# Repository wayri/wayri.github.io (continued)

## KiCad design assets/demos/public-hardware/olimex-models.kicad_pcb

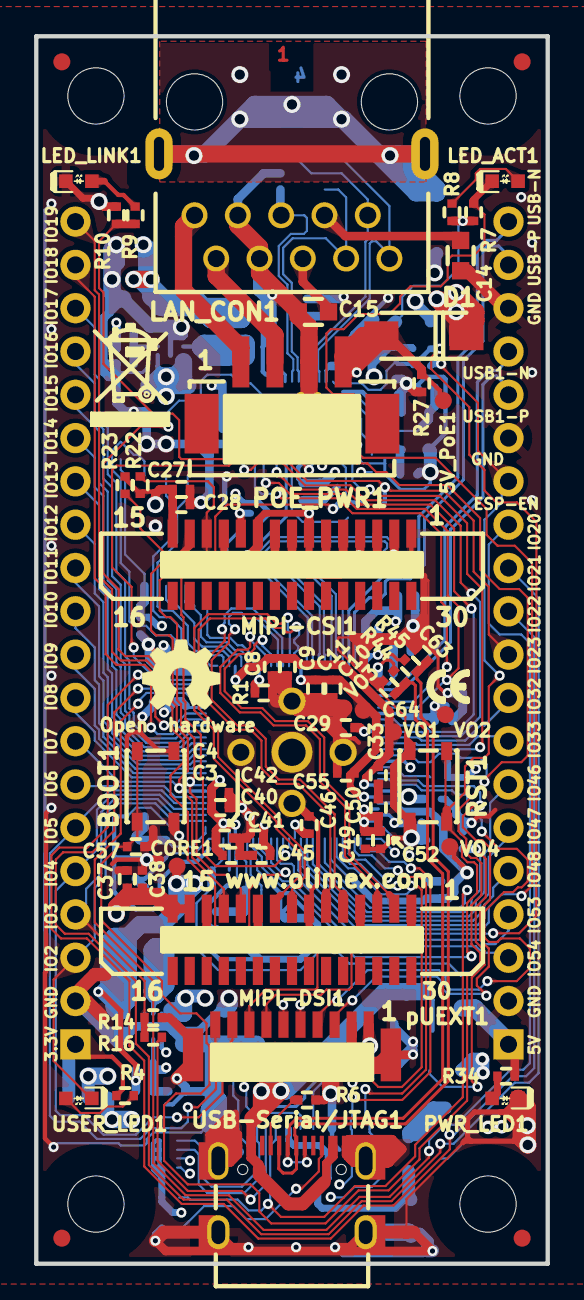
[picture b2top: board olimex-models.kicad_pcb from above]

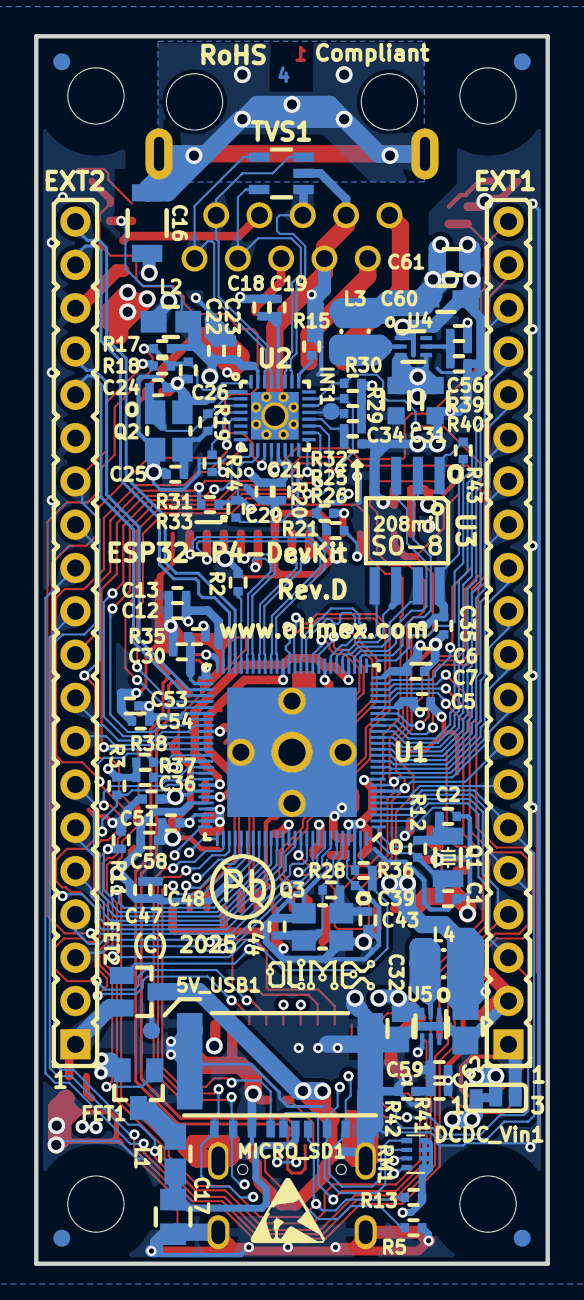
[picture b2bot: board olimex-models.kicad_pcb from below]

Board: 4 copper layers, 30.0 x 72.0 mm, 168 parts (97 on the bottom side), 130 nets.

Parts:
5V_PoE1, 5V_USB1: TESTPAD; TESTPAD_40-ROUND
BOOT1: YTS-A016-X
C1, C2, C43, C44: 22pF/50V/5%/C0G/C0402; C_0402_5MIL_DWS
C3, C6, C18, C20, C22, C27, C37, C40, C49: 10uF/6.3V/20%/X5R/C0402; C_0402_5MIL_DWS
C4, C5, C7, C9, C11, C12, C19, C21, C23, C28, C29, C35, C38, C39, C41, C42, C45, C46, C48, C50, C51, C52, C53: 100nF/10V/20%/X5R/C0402; C_0402_5MIL_DWS
C8, C10, C33, C36, C47, C54, C55, C58: 1uF/6.3V/10%/X5R/C0402; C_0402_5MIL_DWS
C13: 4.7uF/X5R/20%/10V/C0402; C_0402_5MIL_DWS
C14, C15: 100nF/50V/20%/Y5V/C0603; C_0603_5MIL_DWS
C16: 1nF/2000V/10%/X7R/C1206; C_1206_5MIL_DWS_ISO
C17, C62: 47uF/6.3V/20%/X5R/C0805; C_0805_5MIL_DWS
C24, C25: 27pF/50V/5%/C0G/C0402; C_0402_5MIL_DWS
C26: NA(10uF/6.3V/20%/X5R/C0402); C_0402_5MIL_DWS
C30, C57: NA(100nF/10V/20%/X5R/C0402); C_0402_5MIL_DWS
C31, C61: NA(22uF/6.3V/20%/X5R/C0603); C_0603_5MIL_DWS
C32, C34, C60: 22uF/6.3V/20%/X5R/C0603; C_0603_5MIL_DWS
C56, C59: NA(120pF/50V/5%/C0G/C0402); C_0402_5MIL_DWS
C63, C64: NA(150pF/50V/2%/NP0/C0402); C_0402_5MIL_DWS
CORE1: TESTPAD; TESTPAD_40-ROUND
D1: 1N5822/SS34/SMA; SMA-KA
DCDC_Vin1: Closed(1-2); SJ_2_SMALL_12_TIED
EXT1, EXT2: NA(HN1x20); HN1x20
FET1, FET2: IRLML6402TRPbF; SOT23
FID1, FID3, FID5, FID7: Fiducial; Fiducial1x3
FID2, FID4, FID6, FID8: Fiducial; Fiducial1x3_Paste
INT1: TESTPAD; TESTPAD_40-ROUND
L1, L2: 600OHM/2A/UPZ2012E-601-2R0TF/0805; L_0805_5MIL_DWS
L3, L4: 1.0uH/4.2A/DCR=35mR/20%/2.00x1.60x1.00mm/L2016(PI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; L_2016_MM
LAN_CON1: RJP-003TC1(LPJ4112CNL)
LED_ACT1: LED/Yellow/0603; LED_0603_KA
LED_LINK1: LED/Green/0603; LED_0603_KA
Logo_OLIMEX_SMALL_TB: Logo_OLIMEX_SMALL_TB
MH1, MH2, MH3, MH4: Mounting_Hole_NPTH; Mounting_Hole_Drill-3.3mm_Clerance-7mm
MICRO_SD1: TFC-9P-1.7H(ATFFS150A01BR016); uSD(TFC-9P-1.xH(ATFFS150A01BR016))
MIPI-CSI1: FPA-VZA2-15-LF; TE_1-1734248-5
MIPI-DSI1: FPA-VZA2-15-LF; TE_1-1734248-5
POE_PWR1: PH2.0-4AT; PH2.0-4PLB
PWR_LED1: LED/RED/0603; LED_0603_KA
Q1: Q32.768kHz/12.5pF/2P/SMD1206; CM7V-T1A(Crystal_Package-1206_3.20x1.50x0.65mm)
Q2: Q25MHz/18pF/30ppm/4P/3.2x2.5mm(ABM8-25.000MHZ-D2Y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; TSX-3.2x2.5mm_GND(3)
Q3: Q40.000MHz/12pF/10ppm/4P/3.2x2.5x0.70mm(Harmony_E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; TSX-3.2x2.5mm_GND(3)
R1, R2: 4.02k/1%/R0402; R_0402_5MIL_DWS
R3, R7, R10, R13, R14, R24, R25, R32: 4.7k/R0402; R_0402_5MIL_DWS
R4, R8, R9, R22, R23, R34: 2.2k/R0402; R_0402_5MIL_DWS
R5, R6: 5.1k/1%/R0402; R_0402_5MIL_DWS
R11, R20, R27, R36, R37, R38, R43: 10k/R0402; R_0402_5MIL_DWS
R12: 10M/R0402; R_0402_5MIL_DWS
R15: 6.19k/1%/R0402; R_0402_5MIL_DWS
R16, R33, R44, R45: 22R/R0402; R_0402_5MIL_DWS
R17, R21: NA(10k/R0402); R_0402_5MIL_DWS
R18, R28: NA/R0402; R_0402_5MIL_DWS
R19: NA(10M/R0402); R_0402_5MIL_DWS
R26: NA(4.7k/R0402); R_0402_5MIL_DWS
R29, R30: 1.5k/R0402; R_0402_5MIL_DWS
R31: NA(22R/R0402); R_0402_5MIL_DWS
R35: NA(0R/R0402); R_0402_5MIL_DWS
R39: 30.1k/1%/R0402; R_0402_5MIL_DWS
R40: 6.49k/1%/R0402; R_0402_5MIL_DWS
R41, R42: 10.5k/1%/R0402; R_0402_5MIL_DWS
RM1: RMAT_(4x0402)_4.7k; RA0805_(4X0402)_xx_BIGGEROUTPADS
RST1: YTS-A016-X
Sign_Antistatic_150: Sign_Antistatic_150
Sign_CE_Small: CE_Sign_Small
Sign_OSHW_7.3x6.0mm: Sign_OSHW_7.3x6.0mm; Sign_OSHW_7.3x6.0mmn
Sign_PB-Free: Sign_PB-Free
Sign_RecycleBin_1: Sign_RecycleBin_1
TVS1: ESDS314DBVR(SOT-23-5); SOT-23-5
U1: ESP32-P4NRWxx(QFN104); QFN104_10mm×10mm_Pitch_0.35mm
U2: IP101GRR(32-PIN_QFN); QFN32_EP(33)_4.00x4.00x0.80mm_Pitch_0.40mm
U3: W25Q128JVSIQ(16MB); SO-8_208mil
U4: TPS62A02ADRLR(SOT-563-6); SOT-563-6
U5: TLV62585PDRLR(SOT-563-6); SOT-563-6
USB-Serial/JTAG1: USB-C-16P-F(A40-00119-A52-12); USB2.0_TYPE-C(A40-00119-A52-12)_Paste
USER_LED1: LED/Green/0603; LED_0603_KA
VO1, VO2, VO3, VO4: TESTPAD; TESTPAD_40-ROUND
pUEXT1: SH1.0-10P-180D; BM10B-SRSS-TB

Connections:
+1V8: C36.2, C53.2, C54.2, U1.59 (VDDPST), U1.67 (VDDPST), U1.72 (VFB2/VO2), VO2.1 (Pad)
+2.5V: C10.1, C11.1, C55.2, U1.41 (VDD_MIPI_DPHY), U1.73 (VFB3/VO3), VO3.1 (Pad)
+3.3V: C3.1, C4.1, C5.2, C12.1, C13.1, C27.1, C28.1, C29.2, C37.1, C38.1, C40.2, C41.2, C42.2, C45.2, C49.2, C50.2, C52.2, C56.2, C60.1, C61.1, DCDC_Vin1.3, EXT1.1, FET1.2, L2.1, L3.2, MIPI-CSI1.15, MIPI-DSI1.14, MIPI-DSI1.15, R3.2, R4.1, R20.1, R21.1, R22.1, R23.1, R36.1, R37.1, R38.1, R39.2, U1.9 (VDDPST_1), U1.21 (VDDPST_2), U1.51 (VCCA), U1.62 (VDDPST_4), U1.75 (VDDPST_LDO), U1.77 (VDDPST_DCDC), U1.96 (VDDPST_6), U1.101 (VDDA), U1.102 (VBAT), pUEXT1.1
+5V: C31.1, C34.1, D1.1 (K), DCDC_Vin1.1, EXT2.1, FET2.2, R34.2, U4.3 (VIN), U4.4 (EN)
+5VP: 5V_PoE1.1 (Pad), D1.2 (A), FET2.1, POE_PWR1.4, R27.2
+5V_USB: 5V_USB1.1 (Pad), FET2.3, USB-Serial/JTAG1.A4 (VBUS), USB-Serial/JTAG1.A9 (VBUS), USB-Serial/JTAG1.B4 (VBUS), USB-Serial/JTAG1.B9 (VBUS)
/3.3V_PHY: C20.1, C21.1, C22.1, C23.1, L2.2, R7.2, R8.2, R17.1, R24.1, R25.1, R29.1, R30.1, R32.1, U2.13 (VDD_IO), U2.31 (AVDD33)
/50MHz_CLKO: R33.2, U2.14 (RXCLK/50M_CLKO)
/CSI_CLKN: MIPI-CSI1.8, U1.45 (CSI_CLKN)
/CSI_CLKP: MIPI-CSI1.9, U1.44 (CSI_CLKP)
/CSI_DATA0N: MIPI-CSI1.2, U1.42 (CSI_DATAN0)
/CSI_DATA0P: MIPI-CSI1.3, U1.43 (CSI_DATAP0)
/CSI_DATA1N: MIPI-CSI1.5, U1.46 (CSI_DATAN1)
/CSI_DATA1P: MIPI-CSI1.6, U1.47 (CSI_DATAP1)
/CSI_IO0\Reset: MIPI-CSI1.11, R20.2
/CSI_IO1\Strobe: MIPI-CSI1.12, R21.2
/DCDC_Vin: C32.1, DCDC_Vin1.2, U5.3 (VIN)
/DSI_CLKN: MIPI-DSI1.5, U1.37 (DSI_CLKN)
/DSI_CLKP: MIPI-DSI1.6, U1.38 (DSI_CLKP)
/DSI_DATA0N: MIPI-DSI1.8, U1.40 (DSI_DATAN0)
/DSI_DATA0P: MIPI-DSI1.9, U1.39 (DSI_DATAP0)
/DSI_DATA1N: MIPI-DSI1.2, U1.36 (DSI_DATAN1)
/DSI_DATA1P: MIPI-DSI1.3, U1.35 (DSI_DATAP1)
/EN_DCDC: U1.79 (EN_DCDC), U5.4 (EN)
/ESP_EN: C39.2, EXT2.14, R18.1, R36.2, RST1.1, U1.103 (CHIP_PU)
/ESP_LDO_VO1: C8.2, C9.2, C33.1, C35.2, R43.1, U1.30 (VDDPST_3), U1.71 (VFB1/VO1), U3.8 (VCC), VO1.1 (Pad)
/ESP_LDO_VO4: C47.1, C48.1, C58.2, R13.1, RM1.1.2, RM1.2.2, RM1.3.2, RM1.4.2, U1.74 (VFB4/VO4), U1.85 (VDDPST_5), VO4.1 (Pad)
/FB_DCDC: C59.1, R41.1, R42.1, U1.78 (FB_DCDC), U5.5 (FB)
/FLASH_CK: U1.32 (FLASH_CK), U3.6 (CLK)
/FLASH_CS: R43.2, U1.27 (FLASH_CS), U3.1 (#CS)
/FLASH_D: U1.33 (FLASH_D), U3.5 (DI(IO0))
/FLASH_HOLD: U1.31 (FLASH_HOLD), U3.7 (#HOLD(IO3))
/FLASH_Q: U1.28 (FLASH_Q), U3.2 (DO(IO1))
/FLASH_WP: U1.29 (FLASH_WP), U3.3 (#WP(IO2))
/GPIO2\User_Led: EXT1.3, U1.2 (GPIO2/TOUCH_0/MTCK), USER_LED1.1 (K)
/GPIO3\SD_DET: EXT1.4, R14.2, R16.1, U1.3 (GPIO3/TOUCH_1/MTDI)
/GPIO4\SPI_SCK(CLK): EXT1.5, U1.4 (GPIO4/TOUCH_2/MTMS), pUEXT1.9
/GPIO5\SPI_CSn(CS#): EXT1.6, U1.5 (GPIO5/TOUCH_3/MTDO), pUEXT1.10
/GPIO6: EXT1.7, U1.6 (GPIO6/TOUCH_4/GPSPI_SPI2_HOLD)
/GPIO7\I2C_SDA: EXT1.8, MIPI-CSI1.14, MIPI-DSI1.12, R23.2, U1.7 (GPIO7/TOUCH_5/GPSPI_SPI2_CS), pUEXT1.6
/GPIO8\I2C_SCL: EXT1.9, MIPI-CSI1.13, MIPI-DSI1.11, R22.2, U1.8 (GPIO8/TOUCH_6/GPSPI_SPI2_D/UART0_RTS), pUEXT1.5
/GPIO9: EXT1.10, U1.10 (GPIO9/TOUCH_7/GPSPI_SPI2_CK/UART0_CTS)
/GPIO10: EXT1.11, U1.11 (GPIO10/TOUCH_8/GPSPI_SPI2_Q/UART1_TXD)
/GPIO11: EXT1.12, U1.12 (GPIO11/TOUCH_9/GPSPI_SPI2_WP/UART1_RTD)
/GPIO12: EXT1.13, U1.13 (GPIO12/TOUCH_10/UART1_RTS)
/GPIO13: EXT1.14, U1.14 (GPIO13/TOUCH_11/UART0_CTS)
/GPIO14: EXT1.15, U1.15 (GPIO14/TOUCH_12/LP_UART_TXD)
/GPIO15: EXT1.16, U1.16 (GPIO15/TOUCH_13/LP_UART_RXD)
/GPIO16: EXT1.17, U1.17 (GPIO16/ADC0)
/GPIO17: EXT1.18, U1.18 (GPIO17/ADC1)
/GPIO18: EXT1.19, U1.19 (GPIO18/ADC2)
/GPIO19: EXT1.20, U1.20 (GPIO19/ADC3)
/GPIO20: EXT2.13, U1.22 (GPIO20/ADC4)
/GPIO21: EXT2.12, U1.23 (GPIO21/ADC5)
/GPIO22: EXT2.11, U1.24 (GPIO22/ADC6/DBG_PSRAM_CK)
/GPIO23: EXT2.10, R31.1, U1.25 (GPIO23/ADC7/50MHz_ref_clk_out/DBG_PSRAM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)
/GPIO32: EXT2.9, U1.63 (GPIO32/I3CMST_SCL/GPSPI_SPI2_HOLD/EMAC_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)
/GPIO33: EXT2.8, U1.64 (GPIO33/I3CMST_SDA/GPSPI_SPI2_WP/EMAC_PH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)
/GPIO34\RMII_TXD0: U1.65 (GPIO34/GPSPI_SPI2_IO4/EMAC_PHY_TXD0/DBG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), U2.9 (TXD0)
/GPIO35\RMII_TXD1: BOOT1.1, C57.1, R38.2, U1.66 (GPIO35/GPSPI_SPI2_IO5/EMAC_PHY_TXD1/DBG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), U2.8 (TXD1)
/GPIO36: R37.2, U1.68 (GPIO36/GPSPI_SPI2_IO6/EMAC_PHY_TXER/DBG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)
/GPIO46: EXT2.7, U1.88 (GPIO46/SD1_DATA5/EMAC_PHY_RXD0/DBG_PSRA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)
/GPIO47: EXT2.6, U1.89 (GPIO47/SD1_DATA6/EMAC_PHY_RXD1/DBG_PSRA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)
/GPIO48: EXT2.5, U1.90 (GPIO48/SD1_DATA7/EMAC_PHY_RXER)
/GPIO53\SPI_TX(MOSI): EXT2.4, U1.97 (GPIO53/ADC12/EMAC_PHY_RXD1/DBG_FLASH_CK), pUEXT1.8
/GPIO54\SPI_RX(MISO): EXT2.3, U1.98 (GPIO54/ADC13/EMAC_PHY_RXER/DBG_FLASH_D), pUEXT1.7
/LAN_Shield: C16.2, LAN_CON1.0 (Shield)
/LED0\PHY_AD0: LED_ACT1.1 (K), R7.1, U2.11 (LED0/PHY_AD0)
/LED3\PHY_AD3: R9.2, R10.2, U2.12 (LED3/PHY_AD3)
/MDC: R29.2, U1.61 (GPIO31/GPSPI_SPI2_Q/EMAC_PHY_RXER/DBG_P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), U2.22 (MDC)
/MDIO: R30.2, U1.95 (GPIO52/ADC11/EMAC_PHY_RXD0/DBG_FLASH_HO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), U2.23 (MDIO)
/PHY_RSTN: C26.1, R17.2, R18.2, U1.94 (GPIO51/ADC10/EMAC_PHY_RXDV/DBG_FLASH_WP), U2.32 (RESET_N)
/PW+: LAN_CON1.9 (PW+), POE_PWR1.2
/PW-: LAN_CON1.10 (PW-), POE_PWR1.1
/RD+: LAN_CON1.3 (RD+), TVS1.5 (I/O4), U2.27 (MDI_RP)
/RD-: LAN_CON1.6 (RD-), TVS1.1 (I/O1), U2.26 (MDI_RN)
/RMII_CLK: R31.2, R33.1, U1.93 (GPIO50/ADC9/EMAC_RMII_CLK/DBG_FLASH_Q), U2.10 (TXCLK/50M_CLKI)
/RMII_RXD0: U1.58 (GPIO29/GPSPI_SPI2_D/EMAC_PHY_RXD0/DBG_P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), U2.18 (RXD0)
/RMII_RXD1: U1.60 (GPIO30/GPSPI_SPI2_CK/EMAC_PHY_RXD1/DBG_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), U2.17 (RXD1)
/RMII_RXDV: U1.57 (GPIO28/GPSPI_SPI2_CS/EMAC_PHY_RXDV/DBG_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), U2.19 (RXDV/CRS_DV/FX_HEN)
/RMII_TXEN: U1.92 (GPIO49/ADC8/EMAC_PHY_TXEN/DBG_FLASH_CS), U2.5 (TXEN)
/RXER/INTR_32: INT1.1 (Pad), R32.2, U2.21 (RXER/INTR_32)
/SD1_CLK: MICRO_SD1.5 (CLK/SCLK), U1.84 (GPIO43/SD1_CLK/EMAC_PHY_TXER/DBG_PSRAM_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)
/SD1_CMD: MICRO_SD1.3 (CMD/DI), R13.2, U1.86 (GPIO44/SD1_CMD/EMAC_RMII_CLK/DBG_PSRAM_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)
/SD1_D0: MICRO_SD1.7 (DAT0/DO), RM1.3.1, U1.80 (GPIO39/SD1_CDATA0/reference_clock_of_50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)
/SD1_D1: MICRO_SD1.8 (DAT1/RES), RM1.4.1, U1.81 (GPIO40/SD1_CDATA1/EMAC_PHY_TXEN/DBG_PSR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)
/SD1_D2: MICRO_SD1.1 (DAT2/RES), RM1.1.1, U1.82 (GPIO41/SD1_CDATA2/EMAC_PHY_TXD0/DBG_PSR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)
/SD1_D3: MICRO_SD1.2 (CD/DAT3/CS), RM1.2.1, U1.83 (GPIO42/SD1_CDATA3/EMAC_PHY_TXD1/DBG_PSR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)
/SD1_PWR_EN: FET1.1, R11.2, U1.87 (GPIO45/SD1_DATA4/EMAC_PHY_RXDV/DBG_PSRA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)
/SD1_VDD: C17.1, L1.2, MICRO_SD1.4 (VDD)
/SW1: L3.1, U4.2 (SW)
/TD+: LAN_CON1.1 (TD+), TVS1.4 (I/O3), U2.30 (MDI_TP)
/TD-: LAN_CON1.2 (TD-), TVS1.3 (I/O2), U2.29 (MDI_TN)
/UART0_RX: R3.1, U1.70 (GPIO38/UART0_RXD/GPSPI_SPI2_DQS), pUEXT1.4
/UART0_TX: U1.69 (GPIO37/UART0_TXD/GPSPI_SPI2_IO7), pUEXT1.3
/USB1P1_0+: R44.2, U1.53 (GPIO25/USB1P1_P0)
/USB1P1_0-: R45.2, U1.52 (GPIO24/USB1P1_N0)
/USB1P1_0N: C63.1, R45.1, USB-Serial/JTAG1.A7 (DN1), USB-Serial/JTAG1.B7 (DN2)
/USB1P1_0P: C64.1, R44.1, USB-Serial/JTAG1.A6 (DP1), USB-Serial/JTAG1.B6 (DP2)
/USB1P1_1N: EXT2.17, U1.55 (GPIO26/USB1P1_N1)
/USB1P1_1P: EXT2.16, U1.56 (GPIO27/USB1P1_P1)
/USB_DN: EXT2.20, U1.49 (DM)
/USB_DP: EXT2.19, U1.50 (DP)
/VDD_SD: FET1.3, L1.1
GND: BOOT1.2, C1.1, C2.1, C3.2, C4.2, C5.1, C6.2, C7.2, C8.1, C9.1, C10.2, C11.2, C12.2, C13.2, C14.1, C15.1, C16.1, C17.2, C18.2, C19.2, C20.2, C21.2, C22.2, C23.2, C24.1, C25.1, C26.2, C27.2, C28.2, C29.1, C30.1, C31.2, C32.2, C33.2, C34.2, C35.1, C36.1, C37.2, C38.2, C39.1, C40.1, C41.1, C42.1, C43.1, C44.1, C45.1, C46.1, C47.2, C48.2, C49.1, C50.1, C51.1, C52.1, C53.1, C54.1, C55.1, C57.2, C58.1, C60.2, C61.2, C62.2, C63.2, C64.2, EXT1.2, EXT2.2, EXT2.15, EXT2.18, LAN_CON1.7 (GND/NC), LAN_CON1.8 (NC/GND), LED_LINK1.1 (K), MICRO_SD1.6 (GND), MICRO_SD1.CH1 (Card_Housing), MIPI-CSI1.1, MIPI-CSI1.4, MIPI-CSI1.7, MIPI-CSI1.10, MIPI-DSI1.1, MIPI-DSI1.4, MIPI-DSI1.7, MIPI-DSI1.10, MIPI-DSI1.13, POE_PWR1.3, PWR_LED1.1 (K), Q2.3 (case), Q3.3 (case), R1.2, R2.2, R5.1, R6.1, R10.1, R11.1, R14.1, R15.2, R26.1, R27.1, R40.2, R42.2, RST1.2, TVS1.2 (GND), U1.105 (GND), U2.1 (TXER/FXSD), U2.33 (GND), U3.4 (GND), U4.1 (GND), U5.1 (GND), USB-Serial/JTAG1.0 (SHELL), USB-Serial/JTAG1.A1 (GND), USB-Serial/JTAG1.A12 (GND), USB-Serial/JTAG1.B1 (GND), USB-Serial/JTAG1.B12 (GND), pUEXT1.0, pUEXT1.2
unnamed: C15.2, LAN_CON1.5 (RCT)
unnamed: C14.2, LAN_CON1.4 (TCT)
unnamed: LED_ACT1.2 (A), R8.1
unnamed: LED_LINK1.2 (A), R9.1
unnamed: MICRO_SD1.CD1 (Card_Detect), R16.2
unnamed: PWR_LED1.2 (A), R34.1
unnamed: R2.1, U1.48 (CSI_REXT)
unnamed: R1.1, U1.34 (DSI_REXT)
unnamed: C1.2, Q1.1, R12.1, U1.104 (GPIO0/XTAL_32K_N)
unnamed: C2.2, Q1.2, R12.2, U1.1 (GPIO1/XTAL_32K_P)
unnamed: C30.2, R35.2, U1.54 (NC(VDD_HP_1))
unnamed: C44.2, Q3.2, R28.2, U1.99 (XTAL_N)
unnamed: C43.2, Q3.1, R28.1, U1.100 (XTAL_P)
unnamed: R24.2, U2.4 (COL/RMII)
unnamed: R25.2, R26.2, U2.20 (CRS/LEDMOD)
unnamed: R15.1, U2.25 (ISET)
unnamed: C18.1, C19.1, U2.28 (REGOUT)
unnamed: C24.2, Q2.1, R19.2, U2.2 (X1)
unnamed: C25.2, Q2.2, R19.1, U2.3 (X2)
unnamed: C56.1, R39.1, R40.1, U4.5 (FB)
unnamed: L4.1, U5.2 (SW)
unnamed: R6.2, USB-Serial/JTAG1.A5 (CC1)
unnamed: R5.2, USB-Serial/JTAG1.B5 (CC2)
unnamed: R4.2, USER_LED1.2 (A)
VDD_CORE: C6.1, C7.1, C46.2, C51.2, C59.2, C62.1, CORE1.1 (Pad), L4.2, R35.1, R41.2, U1.26 (VDD_HP_0), U1.76 (VDD_HP_2), U1.91 (VDD_HP_3)

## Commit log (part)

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2020-11-05 redo
2020-11-05 revamp
2020-11-05 design
2020-11-05 link
2020-11-05 style
2020-11-15 added projects to cover
    dacard and arduino osci pics
2021-07-26 Changed design
    Full redesign of index and style.
2021-07-26 random article 2 test
2021-07-27 landing text
2021-07-28 Update and rename index.html to index.html#home
2021-07-28 Rename index.html#home to index.html
2026-05-25 Initialize GitHub Pages site with Jekyll and custom Tools
2026-05-25 Fix navigate button and implement clean URL permalinks for GitHub Pages compatibility
2026-05-25 Add social icons to navbar and update links
2026-05-25 Fix syntax errors in tools_expansion and fix pong.html layout and link
2026-05-25 UI updates: blank products tab, fix blog return button, update footer copyright, hide advisor description
2026-05-25 Tools overhaul: Chart.js plots, Web Serial rewrite, world map fix, filter Bode plot
2026-05-25 Add SVG diagrams, fix Chart.js solar sim & filter plots, fix solar text fields, fix Web Serial encoding
2026-05-25 Fix pong payload key, fix rendering bugs, layout, and update links
2026-05-25 Remove BOM from index.html
2026-05-25 Fix CRLF line endings breaking Jekyll and fix pong payload theming/encryption
2026-05-25 Fix pong performance bug, update EE diagrams, fix PV yield inputs
2026-05-25 Fix SVG font rendering, replace image diagrams with SVG, fix Filter tool labels and recommendations
2026-05-25 Update overview page with comprehensive EPS and hardware bio
2026-05-25 Update overview page with kilowatt-scale, DACard details, sensing tech, and advisory roles
2026-05-25 Update overview page with debugging, lab tools, simulation software, ECAD/MCAD, and MLCC converters
2026-05-25 Update satellite advisory text to specify GNSS simulator and magnetic torque rods
2026-05-25 Change budget scope to state policy impact
2026-05-25 Update timeline: KU role to Technical Advisor for EV impact, and NIT role to include grid inverter PCB hardware development
2026-05-25 Update timeline: Revert KU title to Research Analyst / Associate & Technical Advisor, and add DFIG test setup to NIT section
2026-05-25 Update NIT Srinagar timeline tag to accurately reflect Research Hardware Infra & PhD Mentorship
2026-05-25 Update Pixxel Space role: clarify BMS involvement and add internal satellite component advisory
2026-05-25 Update Pixxel Space timeline: Add mention of high-density power regulation modules
2026-05-25 Update timeline: Simplify TIDE center role to just Kashmir University
2026-05-25 Restructure projects: restore github links and categorize explicitly into Hardware and Software
2026-05-25 Fix DACard typo and link; Add animated skills marquee near footer
2026-05-25 Update STM32 PWM post with link to GitHub repo
2026-05-26 Fix PV Simulator, remove SMPS diagram, fix tool units/labels, update Pixxel experience
2026-05-26 Fix drawSolarMap loop for _WMAP object
2026-05-26 Fix PV Simulator SET button and Show All Months toggle
2026-05-26 Fix PV Simulator Show All Months toggle to update chart properly with color coding and legend
2026-05-26 Fix PV Simulator right side controls and map sun line
2026-05-26 Add global standard value suggestions for resistors and capacitors across all tools
2026-05-26 Fix PV Simulator ReferenceError on dec var and increase sun line visibility
2026-05-26 Bust cache for js files, fix filter chart initialization, and correct image path
2026-06-06 Add CATS and Power Logger projects to portfolio
2026-06-06 Update Power Logger description with firmware and host software details
2026-06-06 Make Power Logger description more concise and update tag
2026-06-06 Update call to action at bottom of page with embedded links
2026-06-06 Add current explorations and education sections
2026-06-06 Add Grade A distinction to Masters degree
2026-06-06 Add publication years to publication list
2026-06-06 Add venue tags to publications
2026-06-06 Add live citation fetching via OpenAlex API
2026-06-06 Update OpenAlex API endpoints to exact DOIs
2026-06-06 Separate Blog entry text from Call To Action block
2026-06-06 Implement click-to-copy functionality for Discord username
2026-06-06 Add SEO meta tags, inline SVG Favicon, and Resume download buttons
2026-06-06 Add compiled PDF resume based on portfolio projects
2026-06-06 Update Pixxel Space timeline in PDF resume
2026-06-06 Update resume title to Systems Engineering | Hardware Architecture
2026-06-13 Remove full-stack jargon and use exact systems architect summary
2026-06-13 Remove products page and Explorations section
2026-06-13 Remove basic academic projects
2026-06-13 Enhance homepage layout: add featured tools, latest logs, and project image placeholders
2026-06-13 Replace discord link with personal website in resume
2026-06-13 Enhance resume: Inject hard metrics to Pixxel experience and add missing dates for past roles
2026-06-17 Update portfolio: experience, skills marquee, and R&D projects
2026-06-17 Add SEO, update philosophy and rename blog section
2026-06-17 Consolidate engineering philosophy into a single statement
2026-06-17 Correct Pixxel Space experience details
2026-06-17 Update CTA text with expanded engineering interests
2026-06-17 Add 500W 3-Phase Inverter Case Study
2026-06-17 Fix post date visibility and comprehensively update resume
2026-06-17 Add Mermaid JS rendering for graphs
2026-06-17 Restore physical layer tagline
2026-06-17 Update domain tags and styling
2026-06-17 Update STM32 PWM engineering log
2026-06-17 Add leadership and mentorship tags
2026-06-17 Update leadership details for satellite and inverter projects
2026-06-17 Add leadership detail to core capabilities section
2026-06-17 Replace distracting clock widget with minimal telemetry and add YAWAR hover animation
2026-06-17 Animate hero text, justify bio text, move telemetry widget
2026-06-17 Restore detailed bio content while preserving justified layout
2026-06-17 Convert skill marquee into interactive expanding matrix with rotating icons
2026-06-17 Rename section to Ongoing R&D, Architecture and Projects
2026-06-17 Expand skill matrix to include EPS, HIL, RTOS, DFM, and leadership skills
2026-06-17 Replace lab-heavy bench tools with systems architecture and product lifecycle skills in matrix
2026-06-17 Restructure skill matrix to split architecture and deep-tech instrumentation
2026-06-17 Update project section titles and descriptions
2026-06-17 Expand bio text to full width of container
2026-06-19 Auto-expand skill matrix on scroll using IntersectionObserver
2026-06-19 Fix smooth animation for skill matrix expansion
2026-06-20 Refine bio intro to emphasize bridging application requirements and physical domains
2026-06-20 Refine Flight Heritage and Team Leadership bullet point to accurately reflect roles
2026-06-20 Clarify leadership role on next-gen satellites
2026-06-20 Refine role description for Pixxel Space to emphasize EPS architecture and testing processes
2026-06-20 Optimize CSS performance by removing backdrop-blur over animations and enabling hardware acceleration
2026-06-20 Rename 'Deep-Tech Execution' to 'Core Technical Skills' to align with industry standard terminology
2026-06-20 Add hover effects and GitHub icons to clickable project cards
2026-06-20 Make GitHub icons permanently visible on linked project cards
2026-06-20 Update Satellite EPS & EGSE project card to be more descriptive and comprehensive
2026-06-20 Enhance Satellite EPS & EGSE card with richer layout, bullet points, and icons
2026-06-20 Make linked project cards highly distinctive with backgrounds, watermarks, and rotating icons
2026-06-20 Optimize skill matrix expansion to prevent scroll glitching on fast scrolls
2026-06-20 Dramatically increase linked card animations: larger sweeping watermarks and stronger lift/shadow
2026-06-20 Add parallax image scaling and aggressive card bulging animations for linked projects
